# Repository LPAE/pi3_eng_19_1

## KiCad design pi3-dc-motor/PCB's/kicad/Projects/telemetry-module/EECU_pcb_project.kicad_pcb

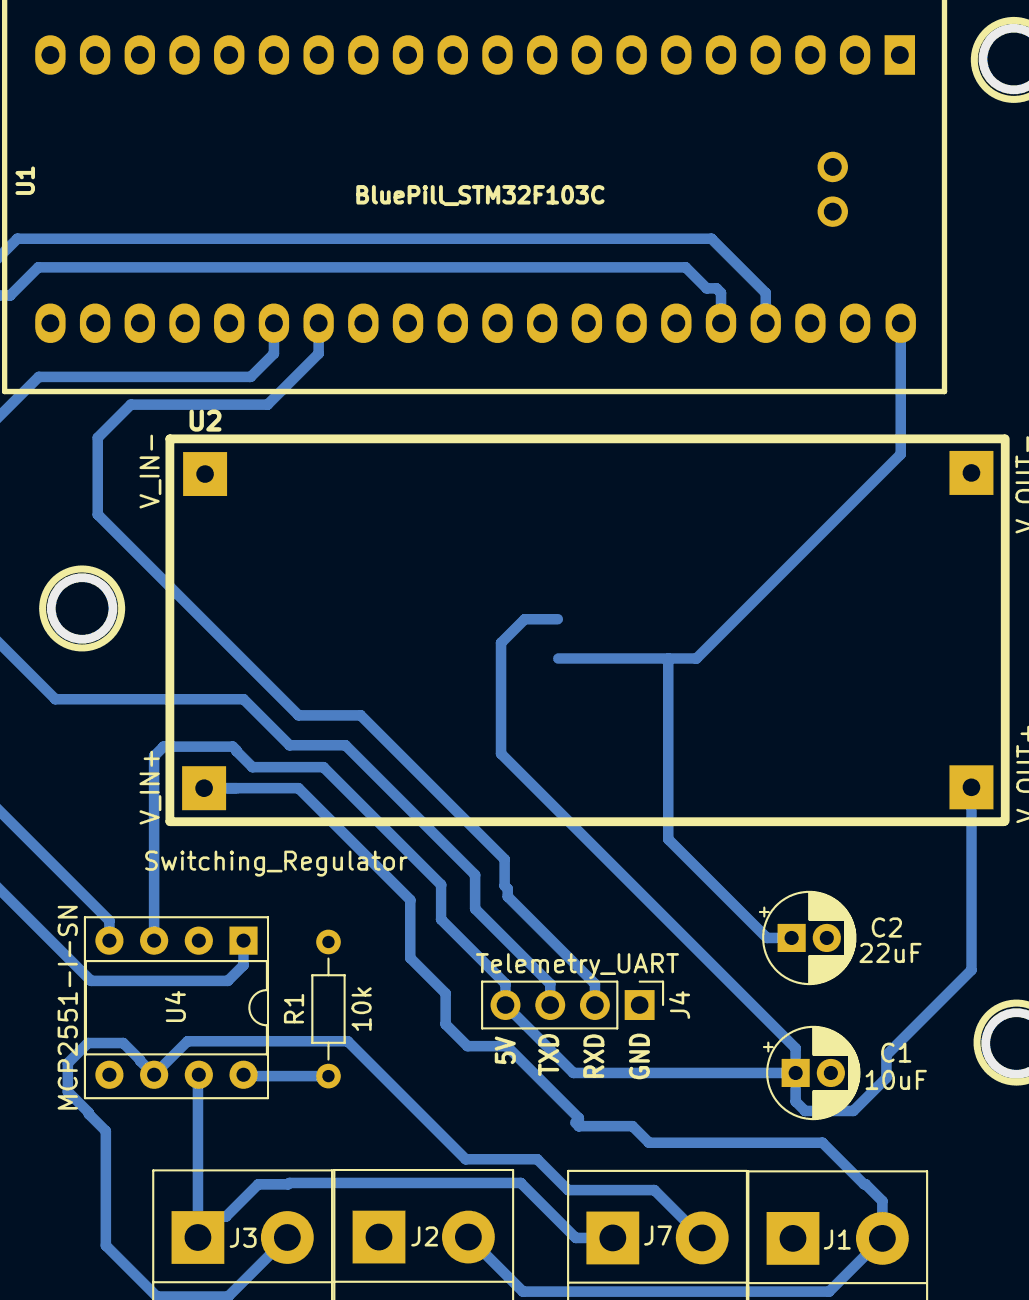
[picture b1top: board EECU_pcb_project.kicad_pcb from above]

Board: 2 copper layers, 12 parts (1 on the bottom side), 11 nets.

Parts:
C1: 10uF; CP_Radial_D5.0mm_P2.00mm
C2: 22uF; CP_Radial_D5.0mm_P2.00mm
J1, J2: BUS_PWR; TerminalBlock_bornier-2_P5.08mm
J3, J7: BUS_CAN; TerminalBlock_bornier-2_P5.08mm
J4: Telemetry_UART; PinHeader_1x04_P2.54mm_Vertical
R1: 10k; R_Axial_DIN0204_L3.6mm_D1.6mm_P7.62mm_Horizontal
U1: BluePill_STM32F103C
U2: Switching_Regulator; switching_regulator
U3: AMS1117-3.3; SOT-223-3_TabPin2
U4: MCP2551-I-SN; DIP-8_W7.62mm_Socket

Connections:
+3V3: C2.1, U1.40, U3.2
+5V: C1.1, J4.4, U2.1, U3.3, U4.3
+12V: J1.2, J2.2, U2.3
CAN_H: J3.1, J7.1, U4.7
CAN_L: J3.2, J7.2, U4.6
CAN_RX: U1.36, U4.4
CAN_TX: U1.37, U4.1
GND: C1.2, C2.2, J1.1, J2.1, J4.1, R1.2, U1.19, U1.20, U1.39, U2.2, U2.4, U3.1, U4.2
unnamed: R1.1, U4.8
USART1_RX: J4.2, U1.27
USART1_TX: J4.3, U1.26

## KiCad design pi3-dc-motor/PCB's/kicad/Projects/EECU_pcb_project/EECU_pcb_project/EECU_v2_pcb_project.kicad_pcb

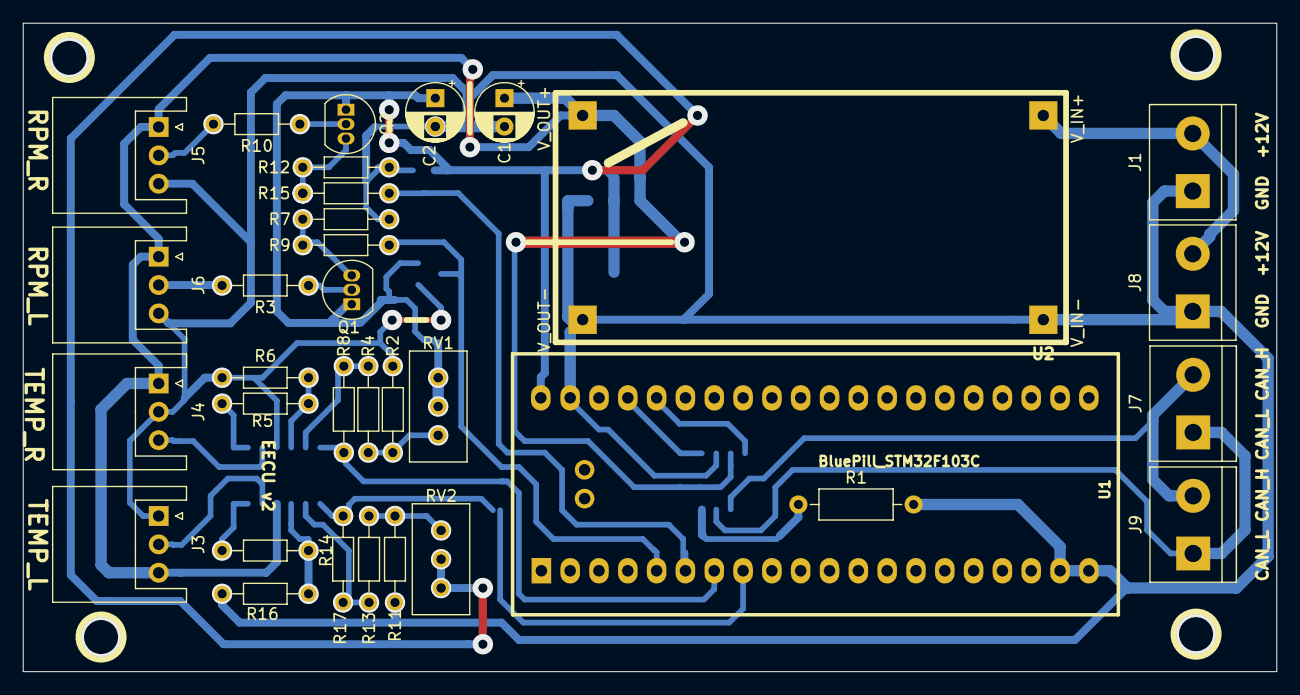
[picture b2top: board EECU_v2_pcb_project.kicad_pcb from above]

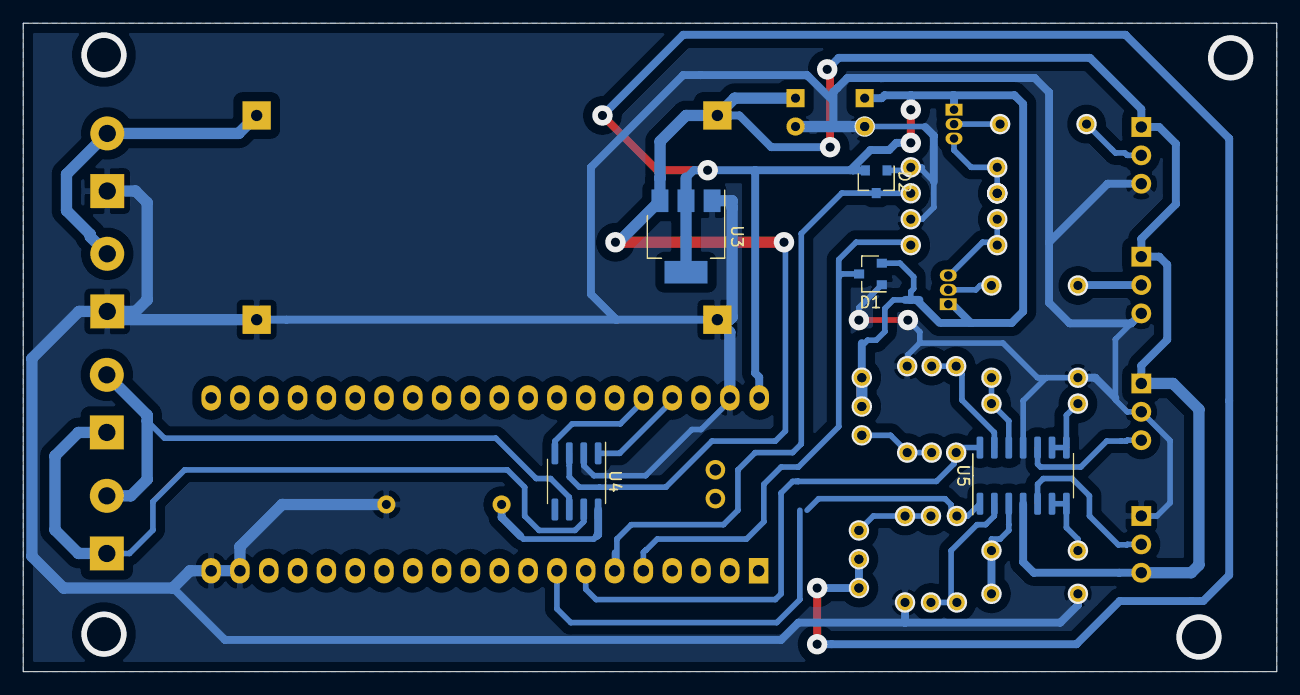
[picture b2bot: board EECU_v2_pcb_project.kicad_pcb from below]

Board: 2 copper layers, 110.5 x 57.2 mm, 38 parts (5 on the bottom side), 29 nets.

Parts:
C1: 10uF; CP_Radial_D5.0mm_P2.50mm
C2: 22uF; CP_Radial_D5.0mm_P2.50mm
D1, D2: BAT54S; SOT-23
J1, J8: BUS_PWR; TerminalBlock_bornier-2_P5.08mm
J3: Temp_Left; JST_XH_S03B-XH-A_03x2.50mm_Angled
J4: Temp_Right; JST_XH_S03B-XH-A_03x2.50mm_Angled
J5: RPM_Right; JST_XH_S03B-XH-A_03x2.50mm_Angled
J6: RPM_Left; JST_XH_S03B-XH-A_03x2.50mm_Angled
J7, J9: BUS_CAN; TerminalBlock_bornier-2_P5.08mm
Q1, Q2: BC547; TO-92_Inline
R1: 10k; R_Axial_DIN0207_L6.3mm_D2.5mm_P10.16mm_Horizontal
R2, R11: 100; R_Axial_DIN0204_L3.6mm_D1.6mm_P7.62mm_Horizontal
R3, R4, R5, R7, R9, R10, R12, R13, R14, R15: 10k; R_Axial_DIN0204_L3.6mm_D1.6mm_P7.62mm_Horizontal
R6, R8, R16, R17: 30k; R_Axial_DIN0204_L3.6mm_D1.6mm_P7.62mm_Horizontal
RV1, RV2: R_POT_TRIM_US; Potentiometer_Bourns_3296W_Vertical
U1: BluePill_STM32F103C
U2: Switching_Regulator; switching_regulator
U3: AMS1117-3.3; SOT-223-3_TabPin2
U4: MCP2551-I-SN; SOIC-8_3.9x4.9mm_P1.27mm
U5: LM324; SOIC-14_3.9x8.7mm_P1.27mm

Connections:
+3V3: C2.1, D1.2, D2.2, Q1.1, Q2.1, RV1.1, RV1.2, RV2.1, RV2.2, U1.40, U3.2
+5V: C1.1, J3.3, J4.1, J5.1, J6.1, U2.2, U3.3, U4.3, U5.4
+12V: J1.2, J8.2, U2.4
CAN_H: J7.1, J9.1, U4.7
CAN_L: J7.2, J9.2, U4.6
CAN_RX: U1.36, U4.4
CAN_TX: U1.37, U4.1
GND: C1.2, C2.2, D1.1, D2.1, J1.1, J3.1, J4.2, J5.3, J6.3, J8.1, R1.2, R2.2, R6.1, R7.2, R11.2, R12.2, R16.1, U1.19, U1.20, U1.39, U2.1, U2.3, U3.1, U4.2, U5.11
unnamed: Q1.2, R3.1
unnamed: Q1.3, R7.1, R9.2
unnamed: Q2.2, R10.1
unnamed: Q2.3, R12.1, R15.2
unnamed: R1.1, U4.8
unnamed: R2.1, R4.1, RV1.3
unnamed: R4.2, R8.1, U5.13
unnamed: R5.1, U5.8, U5.9
unnamed: R5.2, R6.2, U5.12
unnamed: R11.1, R13.1, RV2.3
unnamed: R13.2, R17.1, U5.2
unnamed: R14.1, U5.6, U5.7
unnamed: R14.2, R16.2, U5.3
RPM_IN_LEFT: J6.2, R3.2
RPM_IN_RIGHT: J5.2, R10.2
RPM_OUT_LEFT: D1.3, R9.1, U1.5
RPM_OUT_RIGHT: D2.3, R15.1, U1.6
TEMP_IN_LEFT: J3.2, U5.5
TEMP_IN_RIGHT: J4.3, U5.10
TEMP_OUT_LEFT: R17.2, U1.8, U5.1
TEMP_OUT_RIGHT: R8.2, U1.7, U5.14

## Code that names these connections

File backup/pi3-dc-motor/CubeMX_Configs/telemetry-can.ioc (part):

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Mcu.Name=STM32F103C(8-B)Tx
Mcu.Package=LQFP48
Mcu.UserName=STM32F103C8Tx
PA10.Mode=Asynchronous
PA10.Signal=USART1_RX
PA13.Mode=Serial_Wire
PA13.Signal=SYS_JTMS-SWDIO
PA14.Mode=Serial_Wire
PA14.Signal=SYS_JTCK-SWCLK
PA9.Mode=Asynchronous
PA9.Signal=USART1_TX
PB8.GPIOParameters=GPIO_PuPd
PB8.GPIO_PuPd=GPIO_NOPULL
PB8.Mode=Master
PB8.Signal=CAN_RX
PB9.Mode=Master
PB9.Signal=CAN_TX
PD0-OSC_IN.Mode=HSE-External-Oscillator
PD0-OSC_IN.Signal=RCC_OSC_IN
PD1-OSC_OUT.Mode=HSE-External-Oscillator
PD1-OSC_OUT.Signal=RCC_OSC_OUT
RCC.SYSCLKFreq_VALUE=72000000
RCC.SYSCLKSource=RCC_SYSCLKSOURCE_PLLCLK
board=custom

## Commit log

2019-08-21 fix repo...
2019-08-21 fix repo... ...
